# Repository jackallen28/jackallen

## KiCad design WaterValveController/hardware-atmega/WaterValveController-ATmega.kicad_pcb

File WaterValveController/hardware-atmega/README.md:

# Water Valve Controller: standalone ATmega328P board (rev A1, for review)

A second, separate version of the controller with the Arduino built in. There is no Arduino Nano
module: the board carries an ATmega328P with everything a Nano has around it, so it runs the same
sketch (`../WaterValveController.ino`) unchanged and uploads from the Arduino IDE over USB-C.
The Nano boards in [`../hardware`](../hardware) are not changed by this one.

| | Through-hole Nano board | Mixed Nano board | **ATmega board** |
|---|---|---|---|
| Size | 66 × 76 mm (5016 mm²) | 66 × 69.2 mm (4567 mm²) | **57 × 56 mm (3192 mm²)** |
| Smaller than the through-hole board | | 9% | **36%** |
| Microcontroller | Nano module on sockets | Nano module on sockets | ATmega328P-AU soldered on |
| 5 V supply | TO-220 regulator + heatsink area | TO-220 regulator + heatsink area | TPS54202H buck, 2 mm tall inductor |
| Fuse | ATO blade fuse holder | ATO blade fuse holder | 3 A resettable fuse (PTC) |
| Reverse supply | crowbar diode blows the fuse | crowbar diode blows the fuse | P-MOSFET simply stays off |
| Tallest parts | Nano on sockets, regulator | Nano on sockets, regulator | screw terminals, JST headers (about 10 mm), receiver module |
| Assembly | hand | JLCPCB SMD + through-hole | JLCPCB SMD + a few through-hole connectors |

`images/atmega-copper.png` shows both copper layers (front red, back blue).

## Why these parts (space first)

- **ATmega328P-AU (TQFP-32):** the Arduino Uno / Nano chip, so the pins, the core and the sketch
  stay the same. The QFN version is smaller still, but its pads are hidden under the chip; the board
  size is set by the connectors, not the chip, so the TQFP's visible pins are kept.
- **0603 resistors and capacitors:** the smallest size that is still easy to rework by hand; all
  are JLCPCB basic parts.
- **TPS54202H buck regulator:** about 90% efficient, so it needs no heatsink and the 18 × 19 mm
  heatsink area of the Nano boards is gone. It gives up to 2 A at 5 V for the ATmega, the receiver,
  the flow sensor and an ESP32 (about 0.6 A at most).
- **AO4407A valve switch (SOIC-8):** 14 mΩ, so 0.13 W at the 3 A fuse rating: no heatsink.
- **Resettable 3 A fuse (PTC, 2920 size):** 7.4 × 5 mm instead of the 20 × 7 mm blade holder, and
  nothing to replace after a fault: it resets once the fault is removed. If you would rather keep a
  replaceable blade fuse, say so: the Keystone holder fits at the bottom edge, adding about 4 mm to
  the board length.
- **Reverse-polarity MOSFET (AO4407A):** with the supply connected backwards it simply stays off;
  the Nano boards' crowbar diode blows the fuse instead.
- **Connectors unchanged:** the same 5.08 mm screw terminals and JST-XH headers in the same
  places (12 V in and the main switch on the bottom edge, the valve and flow sensor terminal on the
  top edge), so the wiring is the same as for the Nano boards.

## What makes it an Arduino

| Part | As on a Nano / Uno |
|------|--------------------|
| U4 ATmega328P-AU | the same microcontroller, at 16 MHz |
| Y1 16 MHz crystal + C10, C11 22 pF | the clock |
| C12–C15 100 nF | decoupling on both VCC pins, AVCC and AREF |
| R39 10 kΩ, D4 1N4148W | reset pull-up and clamp (as on the Uno) |
| J9 USB-C, U3 CH340N | USB to serial, as on most Nano boards; R35, R36 5.1 kΩ tell a USB-C charger or computer to supply 5 V |
| C9 100 nF | auto-reset: the IDE resets the ATmega to start the bootloader |
| R37, R38 1 kΩ | serial lines between the CH340N and D0 / D1 |
| D3 B5819W | lets the board run from USB alone for uploads, and stops 5 V flowing back into the computer |
| D5 + R40 | the "L" LED on D13 |
| J10 ICSP | standard 6-pin AVR ISP header, for burning the bootloader once (see Programming) |

Not included, to save space: a reset button (unplugging the power, or uploading, resets it) and a
power LED (the rocker switch's lamp shows the power).

## Pins (unchanged)

| Arduino pin | Use |
|-------------|-----|
| D0 / D1 | USB serial (Serial Monitor) |
| D2 | flow sensor, through R2 1 kΩ, with R1 10 kΩ pull-up and C17 10 nF |
| D4 | button J5 (R3 pull-up, C18 filter) |
| D5, D6, D7 | LEDs 25 / 50 / 100 L on J6–J8, through 330 Ω |
| D8 | valve: Q2 drives Q1's gate |
| D11 | data to the ESP32 (J4 pin 3), divided to 3.24 V by R11 / R12 |
| D12 | data from the ESP32 (J4 pin 4), through R21 1 kΩ |
| D13 | "L" LED |
| A0–A3 | receiver outputs D0–D3, through 1 kΩ, with 100 kΩ pull-downs |

The connectors are the same as on the Nano boards (see [the hardware README](../hardware/README.md#board-connectors)),
plus J9 (USB-C) and J10 (ICSP). The receiver socket U2 is on the right edge; its **GND** end is
nearest the USB socket and its **ANT** end towards the bottom.

## Programming

**Day to day:** once the chip has its bootloader, the board uploads over USB-C like any Arduino:
choose **Tools → Board → Arduino Uno** and the board's port. Windows 10/11, macOS and Linux have
the CH340 driver built in.

**Once, with an external programmer:** the ATmega328P from JLCPCB is blank (no bootloader, running
on its 1 MHz internal clock), so the Arduino bootloader goes in once through the ICSP header **J10**.
J10 has the standard 6-pin AVR ISP pinout, so any AVR ISP programmer plugs straight on:

```
            J10 (looking at the top of the board)
   pin 1  MISO (D12)   ■ ●  pin 2  +5V
   pin 3  SCK  (D13)   ● ●  pin 4  MOSI (D11)
   pin 5  RESET        ● ●  pin 6  GND
   (pin 1 is the square pad)
```

The extra parts on these lines are what an Arduino Uno has (10 kΩ pull-up and 100 nF auto-reset on
RESET, the D13 LED on SCK) plus the ESP divider on MOSI, all light enough for any programmer. J10 is
left empty: solder in a 2 × 3 pin header (2.54 mm), or cut one from a 2 × 40 strip. There is room
around it for a 6-pin ribbon-cable plug.

### Recommended: Pololu USB AVR Programmer v2.1

About A$30 (Core Electronics stocks it as POLOLU-3172). It comes with the 6-pin cable, its default
ISP speed (114 kHz) suits a blank 1 MHz chip, it adapts to 5 V by itself, and the Arduino IDE
supports it.

1. Unplug the ESP32 from J4 (it shares D11 and D12 with the ICSP pins).
2. Power the board from its own USB-C (any USB charger or computer port). The programmer does not
   supply power by default, and the board has more capacitance on 5 V than its power output can start.
3. Plug the 6-pin cable onto J10 with the cable's pin 1 (red stripe / triangle on the plug) on the
   square pad, and the programmer into the computer.
4. In the Arduino IDE: **Tools → Board → Arduino Uno**, **Tools → Programmer → Atmel STK500
   development board**, **Tools → Port →** the programmer's *programming* port (it shows two ports),
   then **Tools → Burn Bootloader**. This sets the fuses (16 MHz crystal, brown-out reset at 2.7 V)
   and writes the Uno bootloader. It takes about a minute.
5. Unplug the programmer and upload the sketch over the board's USB-C as an Arduino Uno.

### Free: your Arduino Nano as the programmer

1. Upload **File → Examples → 11.ArduinoISP → ArduinoISP** to the Nano.
2. Put a 10 µF capacitor between the Nano's RESET and GND (+ leg to RESET), so the IDE does not
   reset the Nano while it is programming.
3. Unplug the ESP32 from J4, then wire the Nano to J10: D12 → pin 1, D13 → pin 3, D11 → pin 4,
   D10 → pin 5, GND → pin 6, and 5V → pin 2 (or leave 5V off and power the board from its USB-C).
4. In the IDE: **Tools → Board → Arduino Uno**, **Tools → Programmer → Arduino as ISP**, the Nano's
   port, then **Tools → Burn Bootloader**.

### Not recommended for this: cheap USBasp clones

They work, but they come with a 10-pin cable (you need a 10-to-6-pin adapter), need a driver
installed with Zadig on Windows, and many still have old firmware that is too fast for a blank chip
unless you fit their "slow SCK" jumper.

The board runs from USB alone for programming and testing; the valve only switches with 12 V
connected.

## Current and heat

The valve current path is laid as fixed 2.5 mm tracks on the top copper (about 4.6 A for a 10 °C
rise with 1 oz copper): 12 V in → fuse → main switch → reverse-polarity MOSFET → up the right
side → valve switch Q1 → J3. It returns through the ground copper poured over both layers and
stitched together. Q1 and Q3 dissipate about 0.13 W each at 3 A; the regulator about 0.3 W at
0.6 A.

## Ordering

The [`JLCPCB/`](JLCPCB/) folder has the gerber zip, the BOM (CSV and `.xlsx` like JLCPCB's sample
BOM) and the CPL file, in the format of JLCPCB's KiCad guide, plus a README with the upload steps.
Every part also has an **LCSC Part #** field, so the KiCad Fabrication Toolkit plugin can make the
same files after you change the design. `WaterValveController-ATmega-KiCad.zip` is the KiCad project
to open and edit (KiCad 7 or later). `WaterValveController-ATmega-assembly.pdf` shows every part's
reference on the board outline (two small parts, R32 and C16, have no room for a silkscreen label).

## Open points to confirm

1. **Fuse:** resettable 3 A PTC (as drawn) or a replaceable blade fuse holder.
2. **Reverse-polarity protection:** MOSFET (as drawn) or the Nano boards' crowbar diode.
3. **Reset button and power LED:** left out to save space; either can be added.
4. **Part numbers:** the passives, crystal, diodes and LED are JLCPCB basic parts that JLCPCB's BOM
   step should confirm (they are marked in `tools/gen_atmega.py`).
5. **Size:** the four M4 corner holes, the 5.08 mm terminals and the four panel connectors down the
   left edge set the size. M3 holes, 3.5 mm terminals or one combined panel connector would take
   it to about 50 × 50 mm.

## Regenerating

The schematic, board and outputs are made by `tools/gen_atmega.py`, which uses the Nano boards'
tools in `../hardware/tools` (KiCad 7, Java 17+ and Freerouting 1.9):

```sh
cd hardware-atmega
python3 tools/gen_atmega.py sch                                  # schematic, checks every net
python3 tools/gen_atmega.py pcb --jar freerouting-1.9.0.jar      # place, route, pour, DRC, gerbers
python3 tools/gen_atmega.py outputs                              # PDF/SVG, BOMs, JLCPCB files, images, zip
```

The circuit is listed part by part in `tools/gen_atmega.py`; placement and the fixed power tracks
are in `tools/atmega_board.py`.

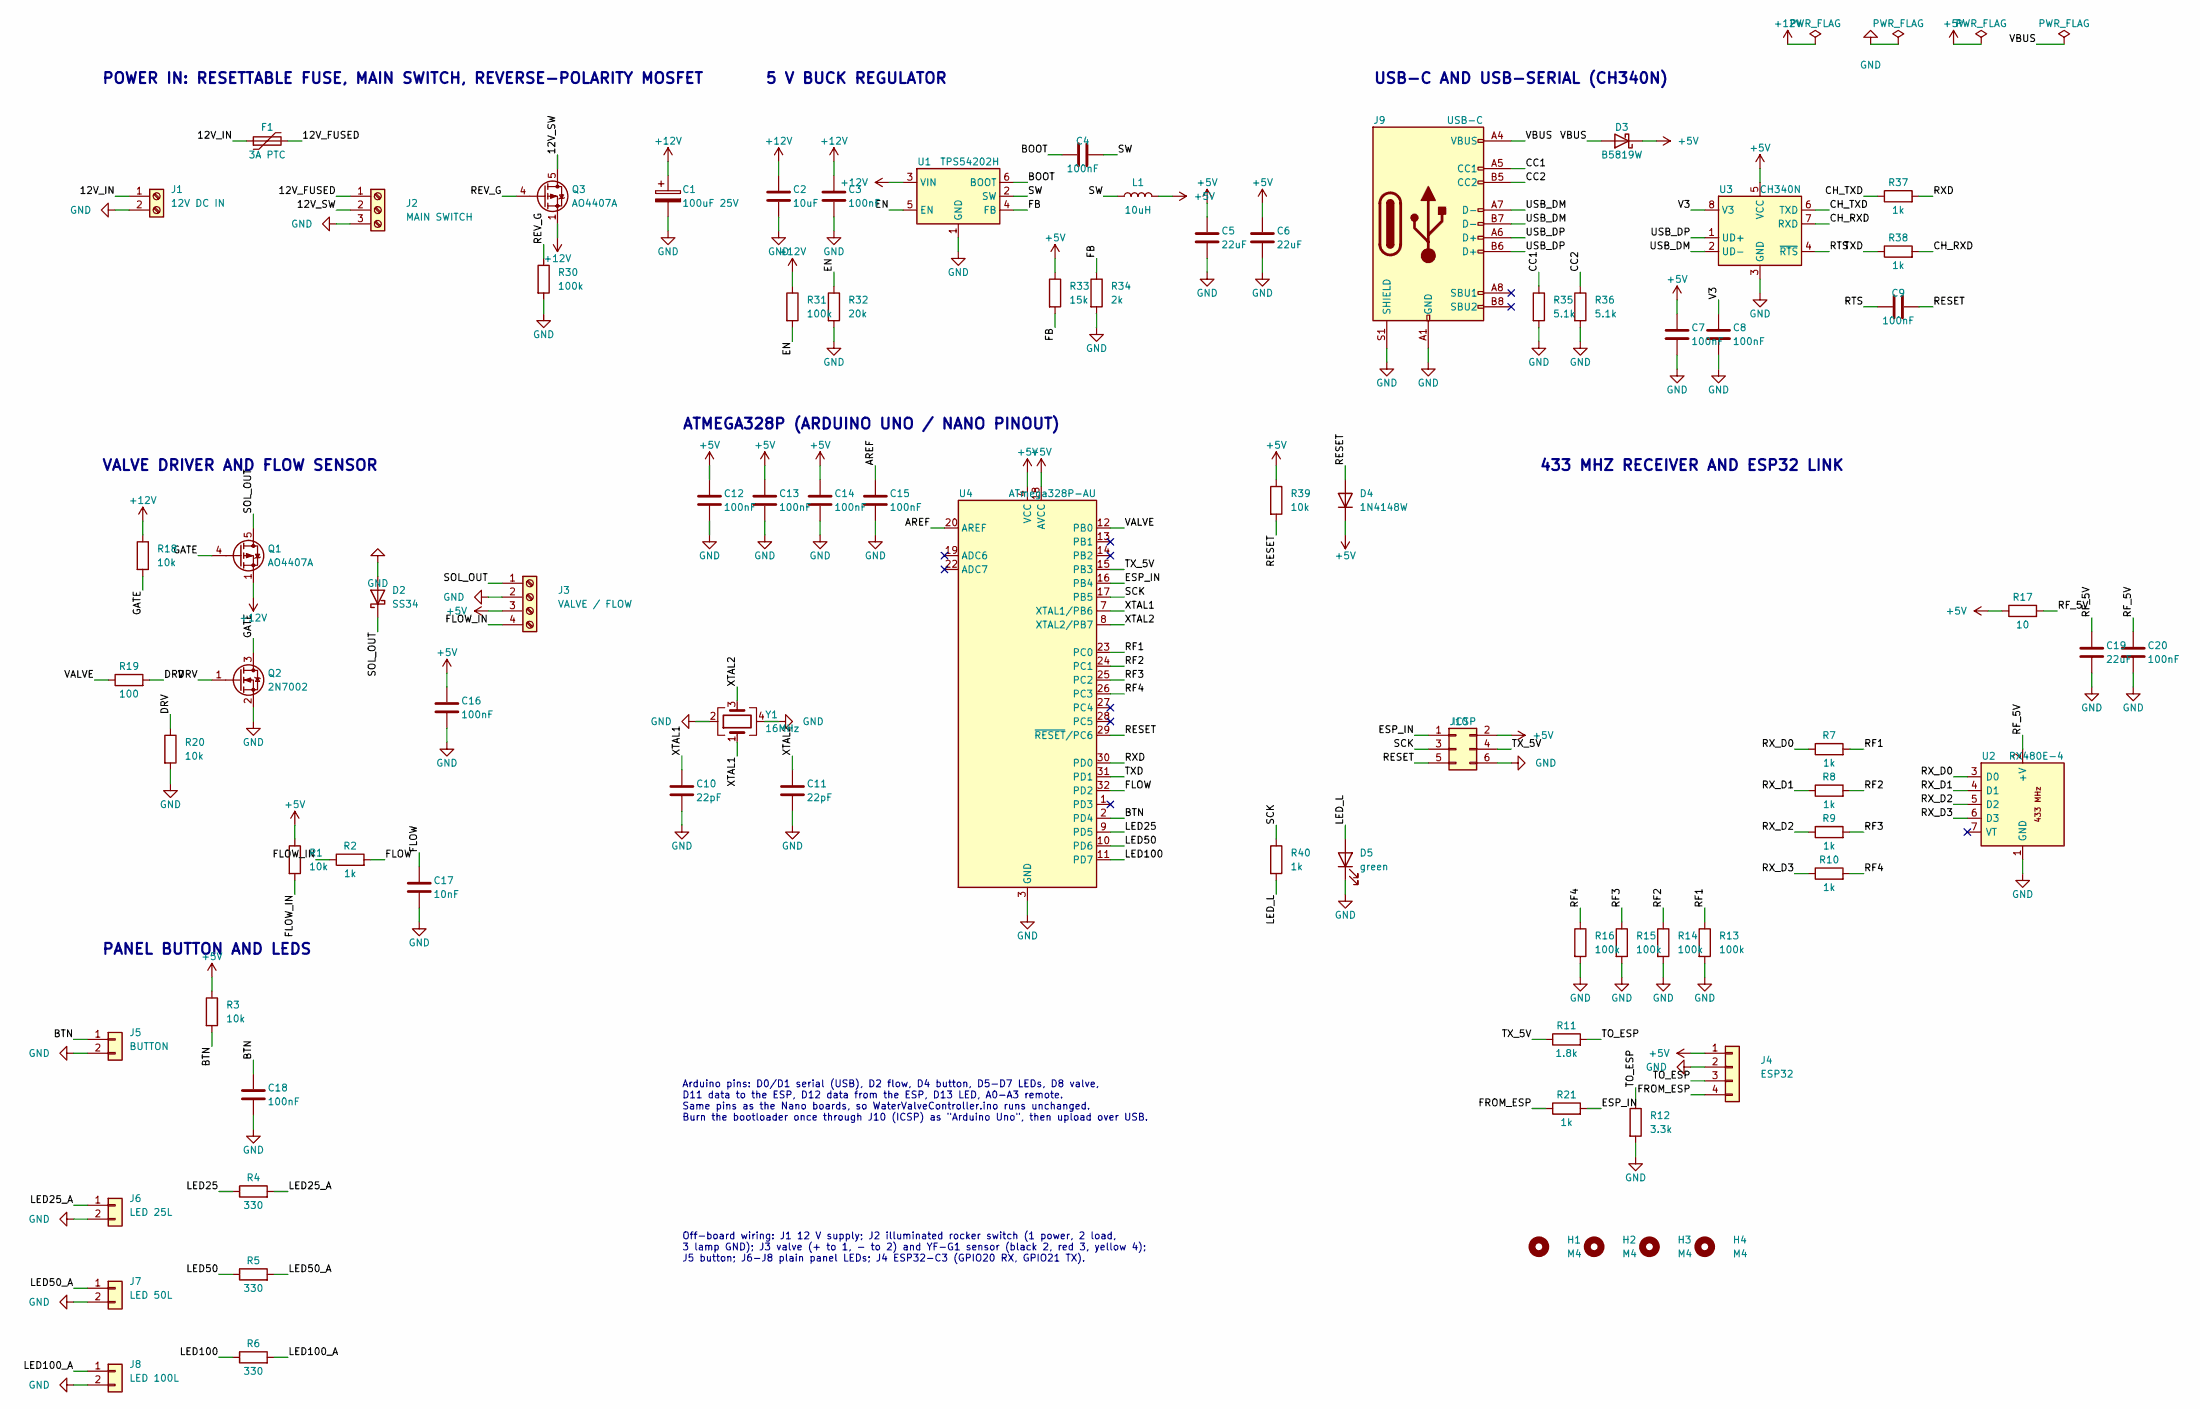
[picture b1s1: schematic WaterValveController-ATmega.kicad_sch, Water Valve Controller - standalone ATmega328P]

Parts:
C1: 100uF 25V; CP_Elec_6.3x7.7; LCSC Part # C22383804
C2: 10uF; C_0805_2012Metric; LCSC Part # C15850
C3, C4, C7, C8, C9, C12, C13, C14, C15, C16, C18, C20: 100nF; C_0603_1608Metric; LCSC Part # C14663
C5, C6, C19: 22uF; C_0805_2012Metric; LCSC Part # C45783
C10, C11: 22pF; C_0603_1608Metric; LCSC Part # C1653
C17: 10nF; C_0603_1608Metric; LCSC Part # C57112
D2: SS34; D_SMA; LCSC Part # C8678
D3: B5819W; D_SOD-123; LCSC Part # C8598
D4: 1N4148W; D_SOD-123; LCSC Part # C81598
D5: green; LED_0603_1608Metric; LCSC Part # C72043
F1: 3A PTC; Fuse_2920_7451Metric; LCSC Part # C22446884
H1, H2, H3, H4: M4; MountingHole_4.3mm_M4
J1: 12V DC IN; TerminalBlock_Phoenix_MKDS-1,5-2-5.08_1x02_P5.08mm_Horizont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; LCSC Part # C474940
J2: MAIN SWITCH; TerminalBlock_Phoenix_MKDS-1,5-3-5.08_1x03_P5.08mm_Horizont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; LCSC Part # C474941
J3: VALVE / FLOW; TerminalBlock_Phoenix_MKDS-1,5-4-5.08_1x04_P5.08mm_Horizont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; LCSC Part # C2827883
J4: ESP32; JST_XH_B4B-XH-A_1x04_P2.50mm_Vertical; LCSC Part # C144395
J5: BUTTON; JST_XH_B2B-XH-A_1x02_P2.50mm_Vertical; LCSC Part # C158012
J6: LED 25L; JST_XH_B2B-XH-A_1x02_P2.50mm_Vertical; LCSC Part # C158012
J7: LED 50L; JST_XH_B2B-XH-A_1x02_P2.50mm_Vertical; LCSC Part # C158012
J8: LED 100L; JST_XH_B2B-XH-A_1x02_P2.50mm_Vertical; LCSC Part # C158012
J9: USB-C; USB_C_Receptacle_HRO_TYPE-C-31-M-12; LCSC Part # C165948
J10: ICSP; PinHeader_2x03_P2.54mm_Vertical
L1: 10uH; L_Sunlord_SWPA4020S; LCSC Part # C135263
Q1, Q3: AO4407A; SOIC-8_3.9x4.9mm_P1.27mm; LCSC Part # C16072
Q2: 2N7002; SOT-23; LCSC Part # C8545
R1, R3, R18, R20, R39: 10k; R_0603_1608Metric; LCSC Part # C25804
R2, R7, R8, R9, R10, R21, R37, R38, R40: 1k; R_0603_1608Metric; LCSC Part # C21190
R4, R5, R6: 330; R_0603_1608Metric; LCSC Part # C23138
R11: 1.8k; R_0603_1608Metric; LCSC Part # C4177
R12: 3.3k; R_0603_1608Metric; LCSC Part # C22978
R13, R14, R15, R16, R30, R31: 100k; R_0603_1608Metric; LCSC Part # C25803
R17: 10; R_0603_1608Metric; LCSC Part # C22859
R19: 100; R_0603_1608Metric; LCSC Part # C22775
R32: 20k; R_0603_1608Metric; LCSC Part # C4184
R33: 15k; R_0603_1608Metric; LCSC Part # C22809
R34: 2k; R_0603_1608Metric; LCSC Part # C22975
R35, R36: 5.1k; R_0603_1608Metric; LCSC Part # C23186
U1: TPS54202H; SOT-23-6; LCSC Part # C527684
U2: RX480E-4; PinSocket_1x07_P2.54mm_Vertical; LCSC Part # C6684533
U3: CH340N; SOP-8_3.9x4.9mm_P1.27mm; LCSC Part # C2977777
U4: ATmega328P-AU; TQFP-32_7x7mm_P0.8mm; LCSC Part # C14877
Y1: 16MHz; Crystal_SMD_3225-4Pin_3.2x2.5mm; LCSC Part # C13738

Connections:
+5V: C5.1, C6.1, C7.1, C12.1, C13.1, C14.1, C16.1, D3.1 (K), D4.1 (K), J3.3, J4.1, J10.2, L1.2, R1.1, R3.1, R17.1, R33.1, R39.1, U3.5 (VCC), U4.4 (VCC), U4.6 (VCC), U4.18 (AVCC)
+12V: C1.1, C2.1, C3.1, Q1.1 (S), Q1.2 (S), Q1.3 (S), Q3.1 (S), Q3.2 (S), Q3.3 (S), R18.1, R31.1, U1.3 (VIN)
/12V_FUSED: F1.2, J2.1
/12V_IN: F1.1, J1.1
/12V_SW: J2.2, Q3.5 (D), Q3.6 (D), Q3.7 (D), Q3.8 (D)
/AREF: C15.1, U4.20 (AREF)
/BOOT: C4.1, U1.6 (BOOT)
/BTN: C18.1, J5.1, R3.2, U4.2 (PD4)
/CC1: J9.A5 (CC1), R35.1
/CC2: J9.B5 (CC2), R36.1
/CH_RXD: R38.2, U3.7 (RXD)
/CH_TXD: R37.1, U3.6 (TXD)
/DRV: Q2.1 (G), R19.2, R20.1
/EN: R31.2, R32.1, U1.5 (EN)
/ESP_IN: J10.1, R21.2, U4.16 (PB4)
/FB: R33.2, R34.1, U1.4 (FB)
/FLOW: C17.1, R2.2, U4.32 (PD2)
/FLOW_IN: J3.4, R1.2, R2.1
/FROM_ESP: J4.4, R21.1
/GATE: Q1.4 (G), Q2.3 (D), R18.2
/LED25: R4.1, U4.9 (PD5)
/LED25_A: J6.1, R4.2
/LED50: R5.1, U4.10 (PD6)
/LED50_A: J7.1, R5.2
/LED100: R6.1, U4.11 (PD7)
/LED100_A: J8.1, R6.2
/LED_L: D5.2 (A), R40.2
/RESET: C9.2, D4.2 (A), J10.5, R39.2, U4.29 (~RESET/PC6)
/REV_G: Q3.4 (G), R30.1
/RF1: R7.2, R13.1, U4.23 (PC0)
/RF2: R8.2, R14.1, U4.24 (PC1)
/RF3: R9.2, R15.1, U4.25 (PC2)
/RF4: R10.2, R16.1, U4.26 (PC3)
/RF_5V: C19.1, C20.1, R17.2, U2.2 (+V)
/RTS: C9.1, U3.4 (~RTS)
/RXD: R37.2, U4.30 (PD0)
/RX_D0: R7.1, U2.3 (D0)
/RX_D1: R8.1, U2.4 (D1)
/RX_D2: R9.1, U2.5 (D2)
/RX_D3: R10.1, U2.6 (D3)
/SCK: J10.3, R40.1, U4.17 (PB5)
/SOL_OUT: D2.1 (K), J3.1, Q1.5 (D), Q1.6 (D), Q1.7 (D), Q1.8 (D)
/SW: C4.2, L1.1, U1.2 (SW)
/TO_ESP: J4.3, R11.2, R12.1
/TXD: R38.1, U4.31 (PD1)
/TX_5V: J10.4, R11.1, U4.15 (PB3)
/USB_DM: J9.A7 (D-), J9.B7 (D-), U3.2 (UD-)
/USB_DP: J9.A6 (D+), J9.B6 (D+), U3.1 (UD+)
/V3: C8.1, U3.8 (V3)
/VALVE: R19.1, U4.12 (PB0)
/VBUS: D3.2 (A), J9.A4 (VBUS), J9.A9 (VBUS), J9.B4 (VBUS), J9.B9 (VBUS)
/XTAL1: C10.1, U4.7 (XTAL1/PB6), Y1.1
/XTAL2: C11.1, U4.8 (XTAL2/PB7), Y1.3
GND: C1.2, C2.2, C3.2, C5.2, C6.2, C7.2, C8.2, C10.2, C11.2, C12.2, C13.2, C14.2, C15.2, C16.2, C17.2, C18.2, C19.2, C20.2, D2.2 (A), D5.1 (K), J1.2, J2.3, J3.2, J4.2, J5.2, J6.2, J7.2, J8.2, J9.A1 (GND), J9.A12 (GND), J9.B1 (GND), J9.B12 (GND), J9.S1 (SHIELD), J10.6, Q2.2 (S), R12.2, R13.2, R14.2, R15.2, R16.2, R20.2, R30.2, R32.2, R34.2, R35.2, R36.2, U1.1 (GND), U2.1 (GND), U3.3 (GND), U4.3 (GND), U4.5 (GND), U4.21 (GND), Y1.2, Y1.4

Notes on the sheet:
POWER IN: RESETTABLE FUSE, MAIN SWITCH, REVERSE-POLARITY MOSFET
5 V BUCK REGULATOR
USB-C AND USB-SERIAL (CH340N)
ATMEGA328P (ARDUINO UNO / NANO PINOUT)
VALVE DRIVER AND FLOW SENSOR
PANEL BUTTON AND LEDS
433 MHZ RECEIVER AND ESP32 LINK
Arduino pins: D0/D1 serial (USB), D2 flow, D4 button, D5-D7 LEDs, D8 valve, D11 data to the ESP, D12 data from the ESP, D13 LED, A0-A3 remote. Same pins as the Nano boards, so WaterValveController.ino runs unchanged. Burn the bootloader once through J10 (ICSP) as "Arduino Uno", then upload over USB.
Off-board wiring: J1 12 V supply; J2 illuminated rocker switch (1 power, 2 load, 3 lamp GND); J3 valve (+ to 1, - to 2) and YF-G1 sensor (black 2, red 3, yellow 4); J5 button; J6-J8 plain panel LEDs; J4 ESP32-C3 (GPIO20 RX, GPIO21 TX).

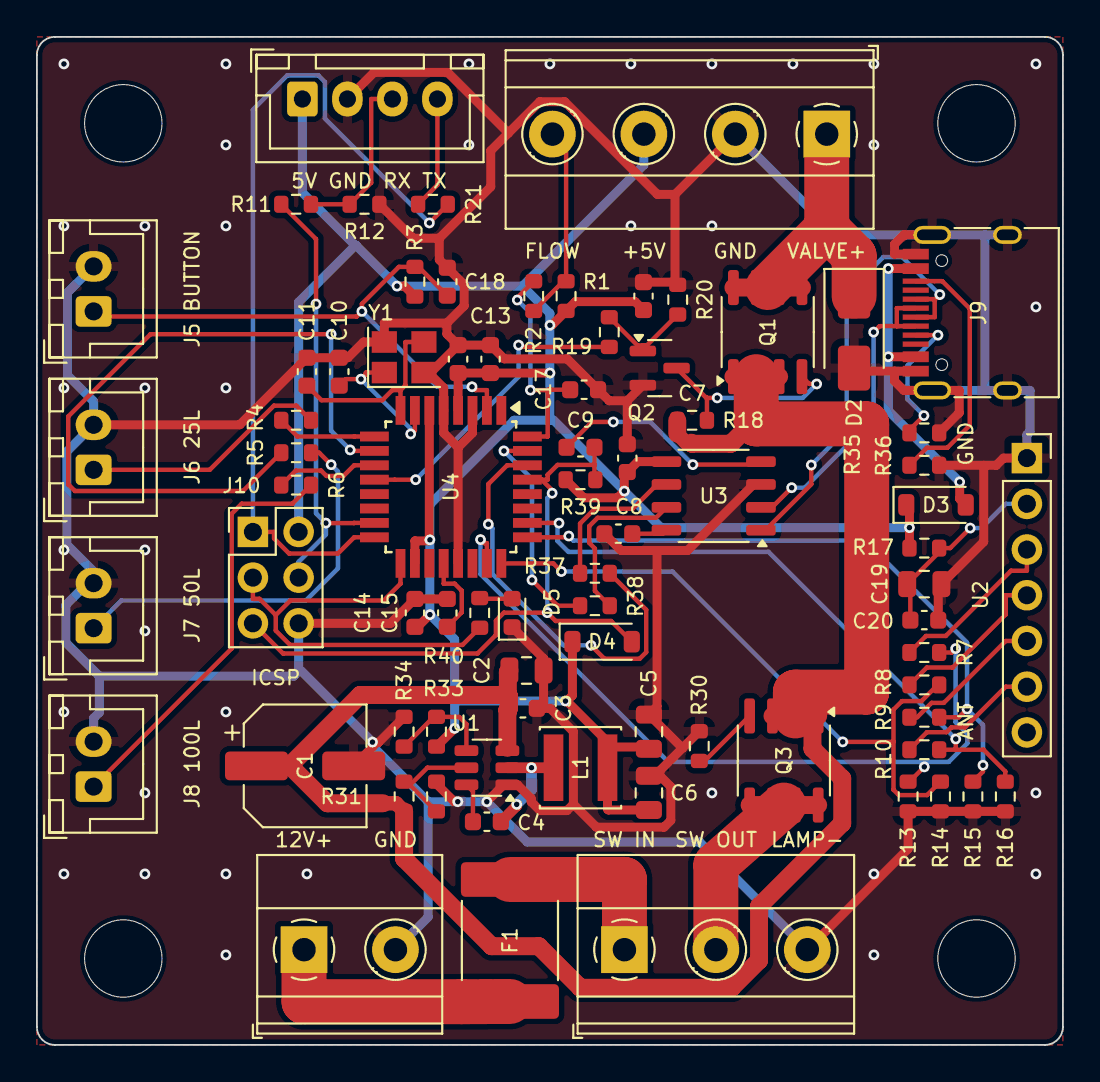
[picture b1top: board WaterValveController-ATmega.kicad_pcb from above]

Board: 2 copper layers, 57.0 x 56.0 mm, 80 parts (0 on the bottom side), 54 nets.

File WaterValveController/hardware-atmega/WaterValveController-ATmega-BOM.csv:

References,Qty,Value,Description,Footprint,JLCPCB / LCSC
C1,1,100uF 25V,"Bulk capacitor, 12 V rail (damps ringing of the supply leads), SMD electrolytic 6.3 x 7.7 mm",CP_Elec_6.3x7.7,C22383804
C2,1,10uF,"U1 input capacitor, 25 V X5R",C_0805_2012Metric,C15850
"C3, C4, C7, C8, C9, C12, C13, C14, C15, C16, C18, C20",12,100nF,Ceramic 100 nF decoupling / filter,C_0603_1608Metric,C14663
"C5, C6",2,22uF,"U1 output capacitor, X5R",C_0805_2012Metric,C45783
"C10, C11",2,22pF,Crystal load capacitor,C_0603_1608Metric,C1653
C17,1,10nF,Flow signal filter (10 us with R2),C_0603_1608Metric,C57112
C19,1,22uF,Receiver supply filter,C_0805_2012Metric,C45783
D2,1,SS34,Flyback diode across the valve output (3 A 40 V Schottky),D_SMA,C8678
D3,1,B5819W,USB power to the 5 V rail (the board runs from USB alone for programming); blocks 5 V back into the computer,D_SOD-123,C8598
D4,1,1N4148W,"Reset clamp, as on the Arduino Uno",D_SOD-123,C81598
D5,1,green,"D13 ""L"" LED, as on an Arduino: blinks when the bootloader starts",LED_0603_1608Metric,C72043
F1,1,3A PTC,"Resettable fuse, 3 A hold, 5 A trip, 30 V (2920). Resets itself once the fault is cleared",Fuse_2920_7451Metric,C22446884
"H1, H2, H3, H4",4,M4,M4 mounting hole,MountingHole_4.3mm_M4,
J1,1,12V DC IN,"12 V DC supply input: 1 = +12 V, 2 = GND. 2-way 5.08 mm screw terminal","TerminalBlock_Phoenix_MKDS-1,5-2-5.08_1x02_P5.08mm_Horizontal",C474940
J2,1,MAIN SWITCH,"Main (rocker) switch: 1 = fused 12 V to the switch, 2 = switched 12 V back, 3 = GND for the switch lamp","TerminalBlock_Phoenix_MKDS-1,5-3-5.08_1x03_P5.08mm_Horizontal",C474941
J3,1,VALVE / FLOW,"Valve and flow sensor: 1 = valve +, 2 = GND (valve - and sensor black), 3 = +5 V (sensor red), 4 = flow signal (sensor yellow)","TerminalBlock_Phoenix_MKDS-1,5-4-5.08_1x04_P5.08mm_Horizontal",C2827883
J4,1,ESP32,"ESP32 link: 1 = 5 V, 2 = GND, 3 = data to the ESP (3.3 V), 4 = data from the ESP. JST-XH 4-pin",JST_XH_B4B-XH-A_1x04_P2.50mm_Vertical,C144395
J5,1,BUTTON,Panel push button (normally open): JST-XH 2-pin,JST_XH_B2B-XH-A_1x02_P2.50mm_Vertical,C158012
J6,1,LED 25L,"25 L panel LED: JST-XH 2-pin, 1 = LED + (anode), 2 = LED - (cathode)",JST_XH_B2B-XH-A_1x02_P2.50mm_Vertical,C158012
J7,1,LED 50L,"50 L panel LED: JST-XH 2-pin, 1 = LED + (anode), 2 = LED - (cathode)",JST_XH_B2B-XH-A_1x02_P2.50mm_Vertical,C158012
J8,1,LED 100L,"100 L panel LED: JST-XH 2-pin, 1 = LED + (anode), 2 = LED - (cathode)",JST_XH_B2B-XH-A_1x02_P2.50mm_Vertical,C158012
J9,1,USB-C,USB-C socket for uploading sketches and the serial monitor (USB 2.0),USB_C_Receptacle_HRO_TYPE-C-31-M-12,C165948
J10,1,ICSP,"ICSP header for burning the bootloader once (MISO, +5V, SCK, MOSI, RESET, GND). Not fitted: plug a 2 x 3 header in only while programming",PinHeader_2x03_P2.54mm_Vertical,
L1,1,10uH,"U1 inductor, 10 uH, 1.6 A, 4 x 4 x 2 mm shielded",L_Sunlord_SWPA4020S,C135263
Q1,1,AO4407A,"High-side P-MOSFET valve switch (-30 V, -12 A, 14 mOhm, SOIC-8): 0.13 W at 3 A, no heatsink",SOIC-8_3.9x4.9mm_P1.27mm,C16072
Q2,1,2N7002,Gate driver for Q1: D8 HIGH switches the valve on,SOT-23,C8545
Q3,1,AO4407A,"Reverse-polarity protection: P-MOSFET in the supply, off if the supply is connected backwards (-30 V, 14 mOhm, SOIC-8)",SOIC-8_3.9x4.9mm_P1.27mm,C16072
"R4, R5, R6",3,330,"LED current limit, about 9 mA",R_0603_1608Metric,C23138
R11,1,1.8k,Divider to the ESP (top): 5 V data to 3.24 V,R_0603_1608Metric,C4177
R12,1,3.3k,Divider to the ESP (bottom),R_0603_1608Metric,C22978
R13,1,100k,Pull-down on A0: no floating input,R_0603_1608Metric,C25803
R14,1,100k,Pull-down on A1: no floating input,R_0603_1608Metric,C25803
R15,1,100k,Pull-down on A2: no floating input,R_0603_1608Metric,C25803
R16,1,100k,Pull-down on A3: no floating input,R_0603_1608Metric,C25803
R17,1,10,Receiver supply filter,R_0603_1608Metric,C22859
R19,1,100,Q2 gate resistor,R_0603_1608Metric,C22775
R30,1,100k,Q3 gate to GND: turns Q3 on with the supply the right way round,R_0603_1608Metric,C25803
R31,1,100k,U1 enable divider (top): U1 starts above about 7 V,R_0603_1608Metric,C25803
R32,1,20k,U1 enable divider (bottom),R_0603_1608Metric,C4184
R33,1,15k,U1 feedback (top): 0.596 V x (1 + 15k / 2k) = 5.07 V,R_0603_1608Metric,C22809
R34,1,2k,U1 feedback (bottom),R_0603_1608Metric,C22975
R35,1,5.1k,USB-C CC1 pull-down: identifies the board as a USB device,R_0603_1608Metric,C23186
R36,1,5.1k,USB-C CC2 pull-down,R_0603_1608Metric,C23186
"R2, R7, R8, R9, R10, R21, R37, R38, R40",9,1k,Series resistor,R_0603_1608Metric,C21190
"R1, R3, R18, R20, R39",5,10k,Pull-up / pull-down,R_0603_1608Metric,C25804
U1,1,TPS54202H,"5 V buck regulator, 4.5-28 V in, 2 A, 500 kHz (TPS54202H, SOT-23-6)",SOT-23-6,C527684
U2,1,RX480E-4,"RX480E-4 433 MHz receiver module (learning code), plugged into a 7-pin socket",PinSocket_1x07_P2.54mm_Vertical,C6684533
U3,1,CH340N,"USB to serial converter (as on an Arduino Nano), internal clock",SOP-8_3.9x4.9mm_P1.27mm,C2977777
U4,1,ATmega328P-AU,"ATmega328P microcontroller (as on an Arduino Uno / Nano), 16 MHz, TQFP-32",TQFP-32_7x7mm_P0.8mm,C14877
Y1,1,16MHz,"16 MHz crystal, 3.2 x 2.5 mm, 20 pF load",Crystal_SMD_3225-4Pin_3.2x2.5mm,C13738
(J10),1,2 x 3 pin header 2.54 mm,"ICSP, only while burning the bootloader",,
(J4),1,JST-XH 4-pin housing + crimped lead,ESP32 link lead,,
(J5-J8),4,JST-XH 2-pin housing + crimped lead,Panel button and LED leads,,
(H1-H4),4,M4 bolt + nut or standoff,Mounting,,

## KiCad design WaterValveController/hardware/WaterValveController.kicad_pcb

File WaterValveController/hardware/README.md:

# Water Valve Controller: schematic and PCBs

A 2-layer carrier board for the Arduino Nano. It brings every connection out to screw terminals or
JST-XH connectors and adds the valve switch, fuse, filtering and protection parts. The 433 MHz
receiver module plugs straight into the board.

The same circuit comes as two boards, so you can compare them:

| | Through-hole (THT) | Mixed SMD + THT |
|---|---|---|
| Folder | this folder | [`smd/`](smd/) |
| Size | **66 × 76 mm** (5016 mm²) | **66 × 69.2 mm** (4567 mm², 9% smaller) |
| Small parts | 1/4 W resistors, ceramic discs, TO-92, DO-201AD | 0805 (hand-solder pads), SOT-23, DPAK, SMC |
| Valve MOSFET Q1 | IRF9540N (TO-220) | IRFR5305 (DPAK) |
| Soldering | everything with an ordinary iron | 0805 parts need a fine tip and tweezers |

The SMD board is only a little smaller because the parts that set the size are the same on both: the
screw terminals, the blade fuse holder, the Nano, the receiver, the JST connectors, the regulator and
its heatsink space, and the electrolytic capacitors (radial cans are smaller than SMD ones, so both
boards use them). On the through-hole board most small parts already lie flat under the Nano.

`images/*-copper.png` show both copper layers (front red, back blue) if you want to check the routing.

## Files

| File | What it is |
|------|------------|
| `WaterValveController-schematic.pdf` / `.svg` | The schematic (the same for both boards) |
| `WaterValveController.kicad_pro`, `.kicad_sch`, `.kicad_pcb` | KiCad 7 project, through-hole board |
| `smd/WaterValveController-SMD.*` | KiCad 7 project, mixed SMD + THT board |
| `JLCPCB/`, `smd/JLCPCB/` | **Order files** for each board: gerber zip, JLCPCB BOM, JLCPCB placement (CPL) file and a README with the upload steps |
| `*-BOM.csv` | Full parts list for that board, with JLCPCB/LCSC part numbers and the off-board parts |
| `*-PCB-top.pdf` | Top copper and silkscreen, printable at 1:1 to check part fits |
| `*-KiCad.zip` | The whole KiCad project in one zip: unzip it and open the `.kicad_pro` in KiCad 7 or later to edit the design |
| `WaterValve.pretty/` | Two board footprints: the socketed Nano and the Keystone 3557-2 fuse holder |
| `tools/` | Scripts that generate all of the above (see the end of this file) |

## Board connectors

All terminals are 5.08 mm screw terminals; J4 to J8 are JST-XH (2.5 mm) headers. Pin 1 of every
connector is the square pad, and the pin names are on the silkscreen.

| Ref | Where | Connector | Pins |
|-----|-------|-----------|------|
| J1 | bottom edge | **12 V IN**, 2-way | 1 = +12 V, 2 = GND |
| J2 | bottom edge | **MAIN SWITCH**, 3-way | 1 = SW IN (fused 12 V to the switch), 2 = SW OUT (switched 12 V back), 3 = LAMP− (GND for the switch lamp) |
| J3 | top edge | **VALVE / FLOW**, 4-way | 1 = VALVE+ (switched 12 V), 2 = GND (valve − and sensor black), 3 = +5V (sensor red), 4 = FLOW (sensor yellow) |
| J4 | top edge | **ESP32**, JST-XH 4-pin | 1 = 5V, 2 = GND, 3 = RX (to ESP GPIO20, 3.3 V), 4 = TX (from ESP GPIO21) |
| J5 | top | **BUTTON**, JST-XH 2-pin | 1 = button, 2 = GND |
| J6–J8 | top | **LED 25L / 50L / 100L**, JST-XH 2-pin | 1 = LED + (anode), 2 = LED − (cathode). The 330 Ω resistors are on the board |
| U2 | left, below the Nano | RX480E-4 receiver, 7-pin socket | 1 GND, 2 +V, 3–6 D0–D3, 7 VT (unused) |

**Main switch.** An illuminated rocker switch has three terminals: power in, load out and lamp. Wire
power in to J2 pin 1, load out to J2 pin 2 and the lamp terminal to J2 pin 3. The 12 V goes through
the fuse before it reaches the switch. Without a switch, link J2 pins 1 and 2.

**Panel LEDs and button.** Use plain LEDs (not "12 V" LEDs with a built-in resistor) and a normally
open momentary button, each on a 2-pin JST-XH lead.

**Receiver orientation.** U2 stands upright in a 7-pin socket. GND is the pin at the module's
learn-button end and VT is at its antenna end. The silkscreen marks **GND END** and **VT / ANT END**:
plugged in backwards, the module puts 5 V onto an output.

**Nano orientation.** The Nano sits across the board on two 15-pin female headers with its USB
connector at the left edge (marked **USB**). Pin 1 (D1/TX) is the square pad at the right.

The sketch uses the same pins as the schematic. With this board, keep `VALVE_DRIVE_ACTIVE_LOW = false`
and `REMOTE_ACTIVE_LOW = false` (the defaults). The sketch is set for a **normally open** valve
(`VALVE_NORMALLY_CLOSED = false`).

## Valve driver

The valve is switched on the board, so no relay module is needed. Q1, a P-channel MOSFET, switches
the 12 V to J3 pin 1 (high-side switching, so the valve's other wire goes to GND).

- **D8 HIGH:** Q2 pulls Q1's gate low and the valve gets 12 V. The normally open valve closes and
  the water stops.
- **D8 LOW, or the Nano unplugged or starting up:** R20 holds Q2 off and R18 holds Q1 off, so the valve
  stays unpowered and open: the water flows. The controller only powers the valve to stop the water,
  and a power cut always leaves the water on.
- **D2** is the flyback diode for the switch-off spike. It sits right at J3. An extra diode on the
  valve terminals does no harm.

At 1 A of valve current Q1 dissipates about 0.12 W (IRF9540N) or 0.07 W (IRFR5305), so it needs no
heatsink. Even at the 3 A fuse rating it is about 1.1 W or 0.6 W: warm, but within both parts'
ratings without a heatsink. Most 12 V valves draw 0.3 to 1 A. A normally open valve is powered for
as long as the water is held off after a limit, so its coil stays warm then; that is normal for
valves rated for continuous duty.

## Power, fuse and switch

J1 → F1 (blade fuse) → J2 pin 1 → main switch → J2 pin 2 → +12 V for the board and the valve.

- **F1** is a Keystone 3557-2 holder for standard ATO/ATC blade fuses (4 legs on a 13.5 × 3.4 mm
  pattern). Use a **3 A** fuse.
- **D1** crowbar: if the supply is connected backwards, D1 conducts and blows the fuse. It sits before
  the switch, so this works with the switch off too.
- **U1:** a TO-220-footprint 5 V regulator. The **R-78E5.0-1.0** switching regulator is recommended:
  it is about 90% efficient and runs cool. An **L7805** also fits, but dropping 12 V to 5 V at the
  ESP32's 0.5 A peaks makes about 3.5 W of heat, so it needs a heatsink.

## Current, heat and weight

- **Copper.** The board uses standard 1 oz (35 µm) copper. The 12 V and valve tracks are 2.5 mm wide:
  about 4.6 A for a 10 °C rise (IPC-2221), more than 1.5 times the 3 A fuse rating. Where a track
  meets a pad it narrows to the pad's width for the last few millimetres (the narrowest is 1.9 mm,
  about 3.8 A, at Q1 on the through-hole board). GND tracks are 1.5 mm (about 3.2 A) and GND is also
  poured over both layers and stitched together with vias, so the valve current has a wide return
  path. +5 V tracks are 1.0 mm (about 2.4 A, against 0.6 A of load). None of the 12 V tracks change
  layer, so no via carries the valve current; vias on the power nets would be 1.2 mm with a 0.6 mm
  hole. 2 oz copper isn't needed.
- **Heatsink space.** The area marked **U1 HEATSINK** on the board (about 18 × 19 mm, above the
  regulator's tab) is kept free of parts, so a TO-220 heatsink fits there. The electrolytic capacitors
  are kept away from it.
- **Weight.** The screw terminals and the 470 µF capacitor sit next to the M4 mounting holes, where
  the board is held. Everything under the Nano is low (flat resistors or SMD parts).
- **Spacing.** Parts have at least 0.4 mm between their courtyards (which already include a margin
  round each part), and the SMD parts use the larger "hand-solder" pads.

## Assembly order

1. The parts that sit under the Nano: on the THT board, the flat resistors R7–R16 and R21; on the SMD
   board, all the 0805 parts inside the Nano's outline. Solder them before the Nano's headers.
2. The rest of the small parts, then the taller ones: Q1, Q2, D1, D2, U1, capacitors, the fuse holder,
   the JST headers and the screw terminals.
3. The two 15-pin female headers for the Nano and the 7-pin socket for the receiver. Plug the Nano in
   with its USB connector at the **USB** mark, and the receiver with its antenna end at **VT / ANT END**.
4. Before plugging in the Nano and receiver, power the board from 12 V and check for 5 V between
   J3 pins 3 and 2.

## Ordering the boards from JLCPCB

Each board has a `JLCPCB` folder ([`JLCPCB/`](JLCPCB/) and [`smd/JLCPCB/`](smd/JLCPCB/)) with
everything JLCPCB needs:

| File | Upload it as |
|------|--------------|
| `*-gerbers.zip` | The PCB: gerbers (Protel file names, no X2 attributes) plus drill files and drill maps |
| `*-BOM-JLCPCB.csv` (or `.xlsx`) | Bill of materials: Comment, Designator, Footprint, JLCPCB Part #, laid out like JLCPCB's sample BOM |
| `*-CPL-JLCPCB.csv` | Pick-and-place file: Designator, Mid X, Mid Y, Rotation, Layer (mm), as in JLCPCB's KiCad guide |

1. On jlcpcb.com, choose **Order now** and upload the gerber zip. Keep the defaults: **2 layers,
   1.6 mm, 1 oz copper**; any colour, HASL or ENIG. The design rules suit any low-cost maker: 0.25 mm
   minimum track, 0.2 mm clearance, 0.6 / 0.3 mm vias.
2. Turn on **PCB Assembly**, top side, and upload the BOM and CPL files.
3. In the BOM step, check every line is matched and in stock. Untick anything you would rather
   solder yourself.
4. In the placement preview, check the diodes, MOSFETs and electrolytic capacitors are the right
   way round (the folder's README lists what to look for), then order.

**Which board for assembly?** The **mixed SMD + THT board** (`smd/JLCPCB/`) is the one to have
JLCPCB assemble: every part in its BOM has a confirmed part number, and its 32 small parts are
machine-placed. The through-hole parts on it (terminals, JST headers, fuse holder, regulator,
electrolytic capacitors) cost extra per solder joint, so you may prefer to solder those yourself.
The through-hole board is nearly all through-hole parts, so it is better ordered bare and hand
soldered; its JLCPCB files are there if you want them (3 parts have no confirmed part number).

Not on either JLCPCB order: the two 15-pin sockets for the Nano (one reference, A1, covers both,
and JLCPCB places one part per reference), the blade fuse, and the off-board parts.

Every part also carries its number in an **LCSC Part #** field, on the schematic symbol and on the
footprint. If you change the design in KiCad 8, 9 or 10, the free **Fabrication Toolkit** plugin
(Plugin and Content Manager) makes the gerbers, BOM and CPL in the same format in one click.

The clear **LOGO / TEXT AREA** (about 17 × 8 mm) has no tracks or vias, only the flat ground pour,
so a silkscreen logo or text printed there will be crisp. In KiCad, place your logo there on the
F.Silkscreen layer. The board's name is on the back silkscreen.

## How the board reduces interference

1. **Valve switch-off spike:** D2 flyback diode right at J3.
2. **Valve current:** 2.5 mm tracks, and GND poured on both layers, so the valve current doesn't
   disturb the Nano's ground.
3. **Decoupling:** C1 470 µF + C2 100 nF on 12 V, C3 100 nF + C4 100 µF at U1, C10 at the Nano's 5V
   pin, C6 at J3 for the flow sensor.
4. **Flow input filter:** R1 10 kΩ pull-up gives clean edges. R2 1 kΩ + C5 10 nF filter out short
   spikes (10 µs time constant, far faster than the sensor's ~108 Hz maximum), and R2 also protects
   the pin. The firmware ignores pulses less than 2 ms apart.
5. **Button and remote inputs:** the button has a 10 kΩ pull-up and a 100 nF filter. Each receiver
   output has a 1 kΩ series resistor (R7–R10) and a 100 kΩ pull-down (R13–R16), so the inputs never
   float. The receiver's supply is filtered by R17 10 Ω + C8 47 µF + C9 100 nF. The firmware
   debounces both.
6. **Supply protection:** fuse F1 and crowbar D1, ahead of the main switch.
7. **ESP link:** R11 1.8 kΩ / R12 3.3 kΩ drop the Nano's 5 V data to 3.24 V for the ESP's 3.3 V
   input. R21 1 kΩ protects D12 on the return line.
8. **Layout:** the receiver's antenna end is at the left edge, away from the valve driver at the top
   right and the regulator at the right. The 12 V input is on the opposite edge from the valve and
   sensor terminal.
9. **Cables:** twist the flow sensor's signal wire with its GND wire and keep it away from the valve
   and 12 V wires. For a long sensor run, use shielded cable with the shield connected to GND at the
   controller end only.

## Regenerating the files

Everything is generated by scripts, so the wiring is checked automatically and the boards can be
re-routed after a change. You need KiCad 7 (`kicad-cli` and its Python module), Java 17+ and
[Freerouting](https://github.com/freerouting/freerouting) 1.9 (2.x also works). On a computer
without a screen, Freerouting 1.9 runs under `xvfb-run`.

```sh
cd hardware
python3 tools/gen_schematic.py .                 # through-hole project
python3 tools/gen_schematic.py smd smd           # mixed SMD + THT project
kicad-cli sch export netlist --format kicadxml -o /tmp/net.xml WaterValveController.kicad_sch
python3 tools/check_netlist.py /tmp/net.xml      # compares every net against the intended design
python3 tools/gen_pcb.py tht --jar freerouting-1.9.0.jar   # place, autoroute, pour, DRC, gerbers
python3 tools/gen_pcb.py smd --jar freerouting-1.9.0.jar
python3 tools/make_jlc.py                        # JLCPCB BOM, CPL and README
python3 tools/make_jlc.py smd
python3 tools/make_outputs.py                    # schematic PDF/SVG, BOM, images, zip
python3 tools/make_outputs.py smd
```

Part positions, the logo and heatsink areas and the silkscreen labels are in `tools/pcb_layout.py`.
The JLCPCB part numbers are in `tools/make_jlc.py`.
`gen_pcb.py --place-only` stops before routing, for checking a new layout.

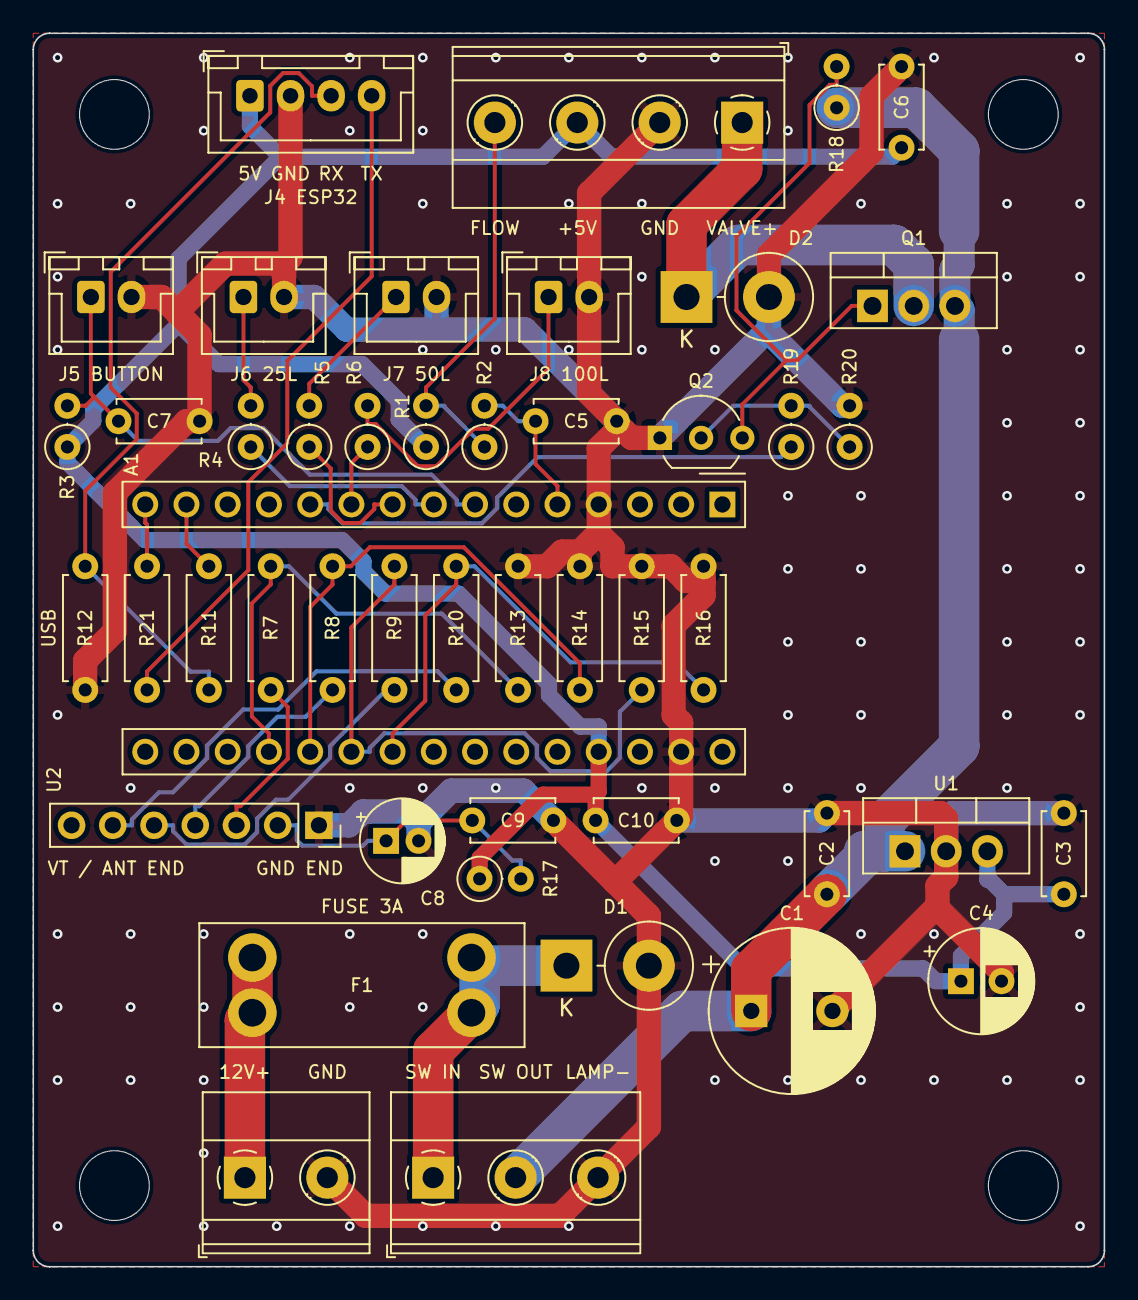
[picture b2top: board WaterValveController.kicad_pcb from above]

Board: 2 copper layers, 66.0 x 76.0 mm, 51 parts (0 on the bottom side), 31 nets.

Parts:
A1: Arduino Nano; Arduino_Nano_Socketed
C1: 470uF 25V; CP_Radial_D10.0mm_P5.00mm
C2, C3, C6, C7, C9, C10: 100nF; C_Disc_D5.0mm_W2.5mm_P5.00mm
C4: 100uF 16V; CP_Radial_D6.3mm_P2.50mm
C5: 10nF; C_Disc_D5.0mm_W2.5mm_P5.00mm
C8: 47uF 16V; CP_Radial_D5.0mm_P2.00mm
D1, D2: 1N5408; D_DO-201AD_P5.08mm_Vertical_KathodeUp
F1: 3A blade (ATO); Fuseholder_Blade_ATO_Keystone_3557-2
H1, H2, H3, H4: M4; MountingHole_4.3mm_M4
J1: 12V DC IN; TerminalBlock_Phoenix_MKDS-1,5-2-5.08_1x02_P5.08mm_Horizont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
J2: MAIN SWITCH; TerminalBlock_Phoenix_MKDS-1,5-3-5.08_1x03_P5.08mm_Horizont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
J3: VALVE / FLOW; TerminalBlock_Phoenix_MKDS-1,5-4-5.08_1x04_P5.08mm_Horizont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
J4: ESP32; JST_XH_B4B-XH-A_1x04_P2.50mm_Vertical
J5: BUTTON; JST_XH_B2B-XH-A_1x02_P2.50mm_Vertical
J6: LED 25L; JST_XH_B2B-XH-A_1x02_P2.50mm_Vertical
J7: LED 50L; JST_XH_B2B-XH-A_1x02_P2.50mm_Vertical
J8: LED 100L; JST_XH_B2B-XH-A_1x02_P2.50mm_Vertical
Q1: IRF9540N; TO-220-3_Vertical
Q2: 2N7000; TO-92_Inline_Wide
R1, R3, R18, R20: 10k; R_Axial_DIN0207_L6.3mm_D2.5mm_P2.54mm_Vertical
R2: 1k; R_Axial_DIN0207_L6.3mm_D2.5mm_P2.54mm_Vertical
R4, R5, R6: 330; R_Axial_DIN0207_L6.3mm_D2.5mm_P2.54mm_Vertical
R7, R8, R9, R10, R21: 1k; R_Axial_DIN0207_L6.3mm_D2.5mm_P7.62mm_Horizontal
R11: 1.8k; R_Axial_DIN0207_L6.3mm_D2.5mm_P7.62mm_Horizontal
R12: 3.3k; R_Axial_DIN0207_L6.3mm_D2.5mm_P7.62mm_Horizontal
R13, R14, R15, R16: 100k; R_Axial_DIN0207_L6.3mm_D2.5mm_P7.62mm_Horizontal
R17: 10R; R_Axial_DIN0207_L6.3mm_D2.5mm_P2.54mm_Vertical
R19: 100; R_Axial_DIN0207_L6.3mm_D2.5mm_P2.54mm_Vertical
U1: R-78E5.0-1.0 or L7805; TO-220-3_Vertical
U2: RX480E-4; PinSocket_1x07_P2.54mm_Vertical

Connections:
+5V: A1.27, C3.1, C4.1, C6.1, C10.1, J3.3, J4.1, R1.1, R3.1, R17.1, U1.3
+12V: C1.1, C2.1, J2.2, Q1.3, R18.1, U1.1
/12V_FUSED: D1.1, F1.2, J2.1
/12V_IN: F1.1, J1.1
/BTN: A1.7, C7.1, J5.1, R3.2
/ESP_IN: A1.15, R21.1
/FLOW: A1.5, C5.1, R2.2
/FLOW_IN: J3.4, R1.2, R2.1
/LED25: A1.8, R4.1
/LED25_A: J6.1, R4.2
/LED50: A1.9, R5.1
/LED50_A: J7.1, R5.2
/LED100: A1.10, R6.1
/LED100_A: J8.1, R6.2
/RF1: A1.19, R7.2, R13.1
/RF2: A1.20, R8.2, R14.1
/RF3: A1.21, R9.2, R15.1
/RF4: A1.22, R10.2, R16.1
/RX_D0: R7.1, U2.3
/RX_D1: R8.1, U2.4
/RX_D2: R9.1, U2.5
/RX_D3: R10.1, U2.6
/SOL_OUT: D2.1, J3.1, Q1.2
/TO_ESP: J4.3, R11.2, R12.1
/TX_5V: A1.14, R11.1
/VALVE: A1.11, R19.1
GND: A1.4, A1.29, C1.2, C2.2, C3.2, C4.2, C5.2, C6.2, C7.2, C8.2, C9.2, C10.2, D1.2, D2.2, J1.2, J2.3, J3.2, J4.2, J5.2, J6.2, J7.2, J8.2, Q2.1, R12.2, R13.2, R14.2, R15.2, R16.2, R20.2, U1.2, U2.1
unnamed: J4.4, R21.2
unnamed: Q1.1, Q2.3, R18.2
unnamed: Q2.2, R19.2, R20.1
unnamed: C8.1, C9.1, R17.2, U2.2

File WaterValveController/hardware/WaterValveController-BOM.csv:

References,Qty,Value,Description,Footprint,Where,JLCPCB / LCSC
A1,1,Arduino Nano,"Arduino Nano v3 (ATmega328P), on 2 x 15 female headers",Arduino_Nano_Socketed,PCB,
C1,1,470uF 25V,"Bulk capacitor, 12 V rail, 105 C electrolytic",CP_Radial_D10.0mm_P5.00mm,PCB,C368591
"C2, C3, C6, C7, C9, C10",6,100nF,"Ceramic 100 nF: decoupling (C2, C3, C6, C9, C10) and button filter (C7)",C_Disc_D5.0mm_W2.5mm_P5.00mm,PCB,C84772
C4,1,100uF 16V,"Electrolytic, 5 V rail",CP_Radial_D6.3mm_P2.50mm,PCB,C911212
C5,1,10nF,Flow signal filter capacitor,C_Disc_D5.0mm_W2.5mm_P5.00mm,PCB,
C8,1,47uF 16V,"Receiver supply filter, electrolytic",CP_Radial_D5.0mm_P2.00mm,PCB,C134586
"D1, D2",2,1N5408,Flyback diode across the valve output: clamps the switch-off spike; Reverse-polarity crowbar: conducts and blows F1 if the supply is reversed,D_DO-201AD_P5.08mm_Vertical_KathodeUp,PCB,C2460
D3,1,25L green,"25 L limit indicator: panel LED (plain, no built-in resistor), JST-XH 2-pin lead",,off-board (panel),
D4,1,50L yellow,"50 L limit indicator: panel LED (plain, no built-in resistor), JST-XH 2-pin lead",,off-board (panel),
D5,1,100L red,"100 L limit indicator: panel LED (plain, no built-in resistor), JST-XH 2-pin lead",,off-board (panel),
F1,1,3A blade (ATO),PCB holder for standard ATO/ATC blade fuses (Keystone 3557-2) + 3 A blade fuse,Fuseholder_Blade_ATO_Keystone_3557-2,PCB,C352820
J1,1,12V DC IN,"12 V DC supply input: 1 = +12 V, 2 = GND. 2-way 5.08 mm screw terminal","TerminalBlock_Phoenix_MKDS-1,5-2-5.08_1x02_P5.08mm_Horizontal",PCB,C474940
J2,1,MAIN SWITCH,"Main (rocker) switch: 1 = fused 12 V to the switch, 2 = switched 12 V back, 3 = GND for the switch lamp","TerminalBlock_Phoenix_MKDS-1,5-3-5.08_1x03_P5.08mm_Horizontal",PCB,C474941
J3,1,VALVE / FLOW,"1 = valve + (switched 12 V), 2 = GND (valve - and sensor black), 3 = +5V (sensor red), 4 = sensor signal (yellow). 4-way 5.08 mm screw terminal","TerminalBlock_Phoenix_MKDS-1,5-4-5.08_1x04_P5.08mm_Horizontal",PCB,C2827883
J4,1,ESP32,"ESP32-C3-Zero link: 1 = +5V (ESP 5V pin), 2 = GND, 3 = data to ESP (3.3 V, ESP RX, GPIO20), 4 = data from ESP (ESP TX, GPIO21). JST-XH 4-pin",JST_XH_B4B-XH-A_1x04_P2.50mm_Vertical,PCB,C144395
J5,1,BUTTON,"Panel push button (MODE / CAL): 1 = button, 2 = GND. JST-XH 2-pin",JST_XH_B2B-XH-A_1x02_P2.50mm_Vertical,PCB,C158012
J6,1,LED 25L,"Panel LED for the 25 L limit: 1 = LED + (anode), 2 = LED - (cathode). JST-XH 2-pin",JST_XH_B2B-XH-A_1x02_P2.50mm_Vertical,PCB,C158012
J7,1,LED 50L,"Panel LED for the 50 L limit: 1 = LED + (anode), 2 = LED - (cathode). JST-XH 2-pin",JST_XH_B2B-XH-A_1x02_P2.50mm_Vertical,PCB,C158012
J8,1,LED 100L,"Panel LED for the 100 L limit: 1 = LED + (anode), 2 = LED - (cathode). JST-XH 2-pin",JST_XH_B2B-XH-A_1x02_P2.50mm_Vertical,PCB,C158012
Q1,1,IRF9540N,"High-side P-MOSFET valve switch (-100 V, -23 A, TO-220; no heatsink needed below 3 A)",TO-220-3_Vertical,PCB,C2575
Q2,1,2N7000,Logic-level N-MOSFET that drives the Q1 gate from D8,TO-92_Inline_Wide,PCB,C232838
"R1, R3, R18, R20",4,10k,"Pull-ups: flow signal (R1), button (R3), Q1 gate (R18); Q2 gate pull-down (R20)",R_Axial_DIN0207_L6.3mm_D2.5mm_P2.54mm_Vertical,PCB,C57436
R2,1,1k,Flow signal series resistor (RC filter / pin protection),R_Axial_DIN0207_L6.3mm_D2.5mm_P2.54mm_Vertical,PCB,C57435
"R4, R5, R6",3,330,"LED current limit, about 9 mA",R_Axial_DIN0207_L6.3mm_D2.5mm_P2.54mm_Vertical,PCB,C58608
"R7, R8, R9, R10, R21",5,1k,Data from ESP: series resistor (pin protection); Remote channel series resistor,R_Axial_DIN0207_L6.3mm_D2.5mm_P7.62mm_Horizontal,PCB,C57435
R11,1,1.8k,Data to ESP divider (top),R_Axial_DIN0207_L6.3mm_D2.5mm_P7.62mm_Horizontal,PCB,
R12,1,3.3k,"Data to ESP divider (bottom), 5 V -> 3.24 V",R_Axial_DIN0207_L6.3mm_D2.5mm_P7.62mm_Horizontal,PCB,
"R13, R14, R15, R16",4,100k,Remote channel pull-down,R_Axial_DIN0207_L6.3mm_D2.5mm_P7.62mm_Horizontal,PCB,C58597
R17,1,10R,Receiver supply filter resistor,R_Axial_DIN0207_L6.3mm_D2.5mm_P2.54mm_Vertical,PCB,C57437
R19,1,100,Q2 gate resistor,R_Axial_DIN0207_L6.3mm_D2.5mm_P2.54mm_Vertical,PCB,C57438
SW1,1,MODE / CAL,"Panel momentary push button (normally open), with a JST-XH 2-pin lead to J5",,off-board (panel),
SW2,1,"Rocker switch, 12 V lamp","Illuminated SPST rocker switch, 12 V lamp, rated 5 A or more (panel mount)",,off-board (panel),
U1,1,R-78E5.0-1.0 or L7805,"5 V regulator, TO-220 pinout IN-GND-OUT: R-78E5.0-1.0 switcher (recommended, runs cool), or L7805 with a heatsink",TO-220-3_Vertical,PCB,C3033024
U2,1,RX480E-4,"RX480E-4 receiver module on a 1x7 female header. Pins: 1 GND, 2 +V, 3-6 D0-D3, 7 VT",PinSocket_1x07_P2.54mm_Vertical,PCB,
(A1),2,15-pin female header 2.54 mm,Sockets for the Nano. Solder the parts that sit under the Nano first,,PCB,C2897378
(U2),1,7-pin female header 2.54 mm,Socket for the RX480E-4 receiver module,,PCB,C6684533
(F1),1,3 A ATO/ATC blade fuse,Standard automotive blade fuse for the F1 holder,,PCB
(J4),1,JST-XH 4-pin housing + crimped lead,ESP32 link lead,,off-board
(J5-J8),4,JST-XH 2-pin housing + crimped lead,Leads to the panel button and LEDs,,off-board
(U1),1,TO-220 heatsink,Only needed with an L7805; fits the marked area (18 x 19 mm),,PCB
(H1-H4),4,M4 bolt + nut or standoff,Mounting,,
